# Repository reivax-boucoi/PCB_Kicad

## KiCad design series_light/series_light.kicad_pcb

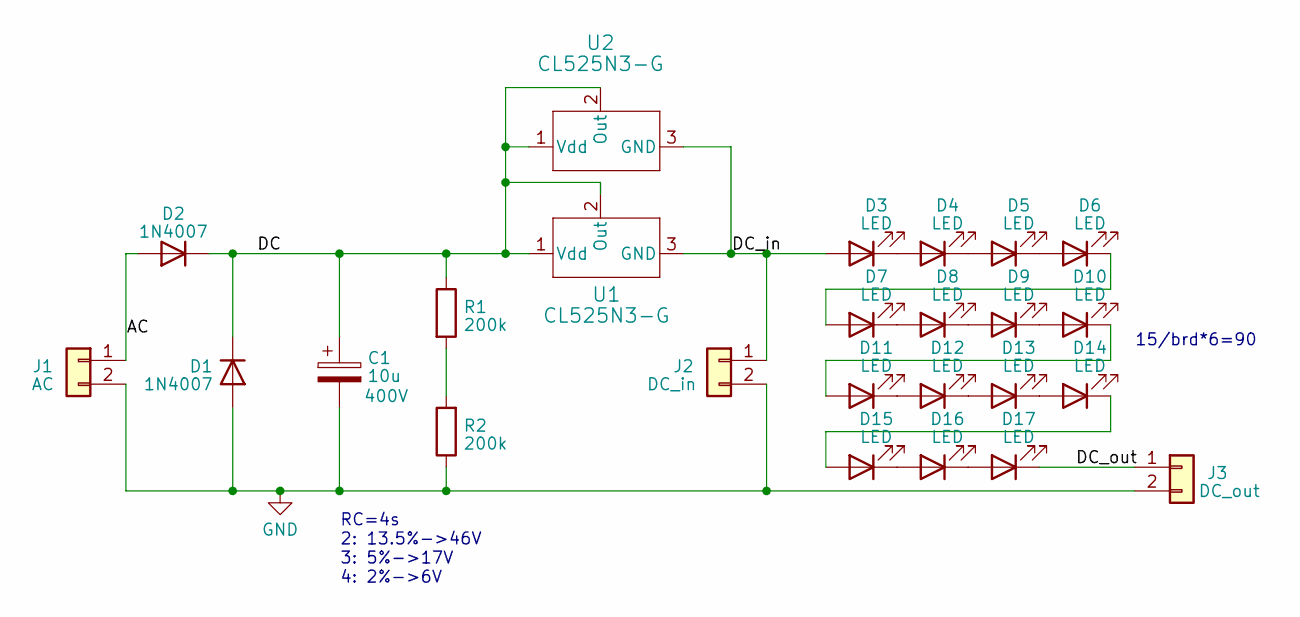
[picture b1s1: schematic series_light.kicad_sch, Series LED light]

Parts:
C1: 10u; Board_edge_cap_P5mm_D10mm; Voltage 400V
D1, D2: 1N4007; D_SMA
D3, D4, D5, D6, D7, D8, D9, D10, D11, D12, D13, D14, D15, D16, D17: LED; LED_PLCC_2835
J1: AC; TerminalBlock_bornier-2_P5.08mm
J2: DC_in; Board_chain_Conn
J3: DC_out; Board_chain_Conn
R1, R2: 200k; R_0805_2012Metric
U1, U2: CL525N3-G; TO-92

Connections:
/AC: D2.2 (A), J1.1
/DC: C1.1, D1.1 (K), D2.1 (K), R1.1, U1.1 (Vdd), U1.2 (Out), U2.1 (Vdd), U2.2 (Out)
/DC_in: D3.2 (A), J2.1, U1.3 (GND), U2.3 (GND)
/DC_out: D17.1 (K), J3.1
GND: C1.2, D1.2 (A), J1.2, J2.2, J3.2, R2.1
unnamed: D3.1 (K), D4.2 (A)
unnamed: D4.1 (K), D5.2 (A)
unnamed: D5.1 (K), D6.2 (A)
unnamed: D6.1 (K), D7.2 (A)
unnamed: D7.1 (K), D8.2 (A)
unnamed: D8.1 (K), D9.2 (A)
unnamed: D9.1 (K), D10.2 (A)
unnamed: D10.1 (K), D11.2 (A)
unnamed: D11.1 (K), D12.2 (A)
unnamed: D12.1 (K), D13.2 (A)
unnamed: D13.1 (K), D14.2 (A)
unnamed: D14.1 (K), D15.2 (A)
unnamed: D15.1 (K), D16.2 (A)
unnamed: D16.1 (K), D17.2 (A)
unnamed: R1.2, R2.2

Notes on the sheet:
RC=4s 2: 13.5%->46V 3: 5%->17V 4: 2%->6V
15/brd*6=90

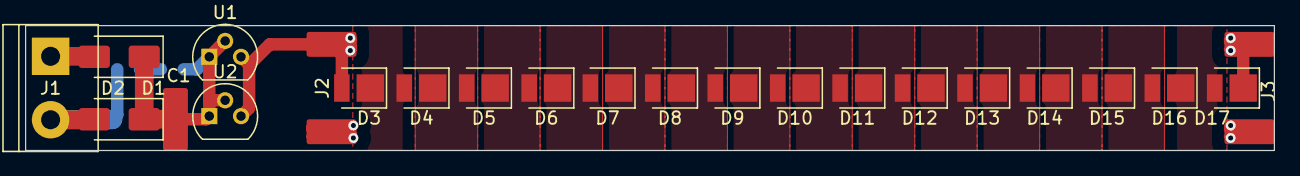
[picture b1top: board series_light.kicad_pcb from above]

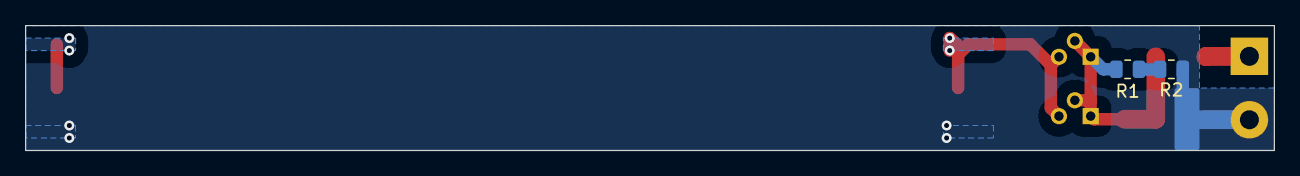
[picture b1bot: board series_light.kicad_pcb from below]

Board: 2 copper layers, 100.0 x 10.0 mm, 25 parts (2 on the bottom side), 20 nets.

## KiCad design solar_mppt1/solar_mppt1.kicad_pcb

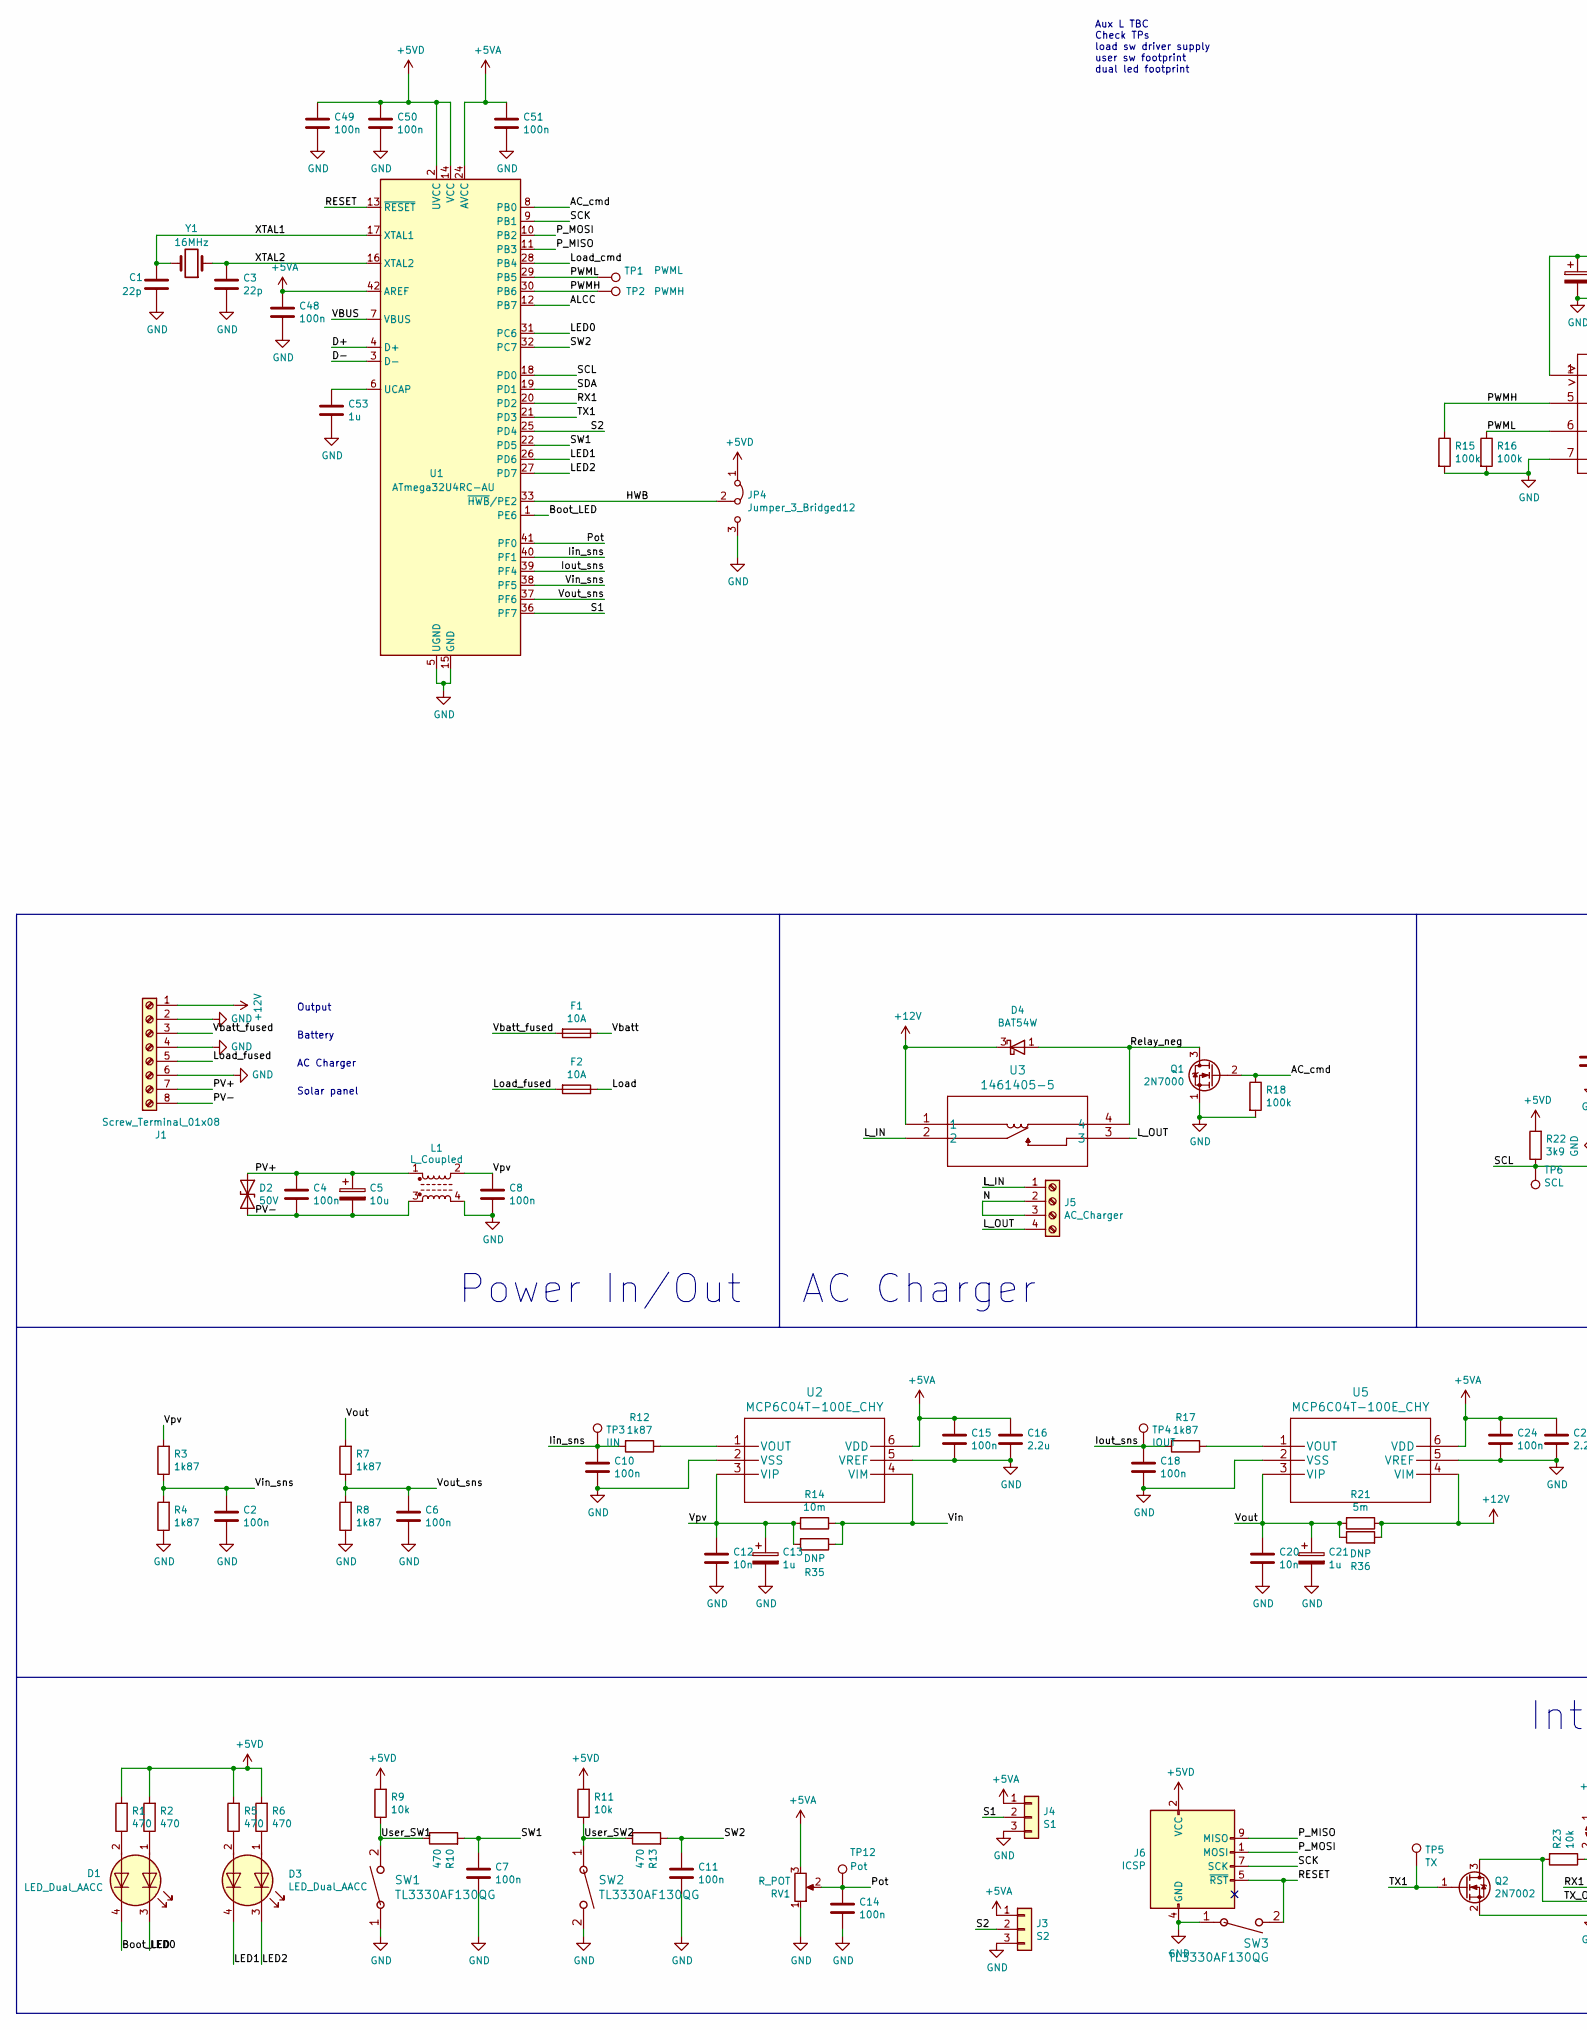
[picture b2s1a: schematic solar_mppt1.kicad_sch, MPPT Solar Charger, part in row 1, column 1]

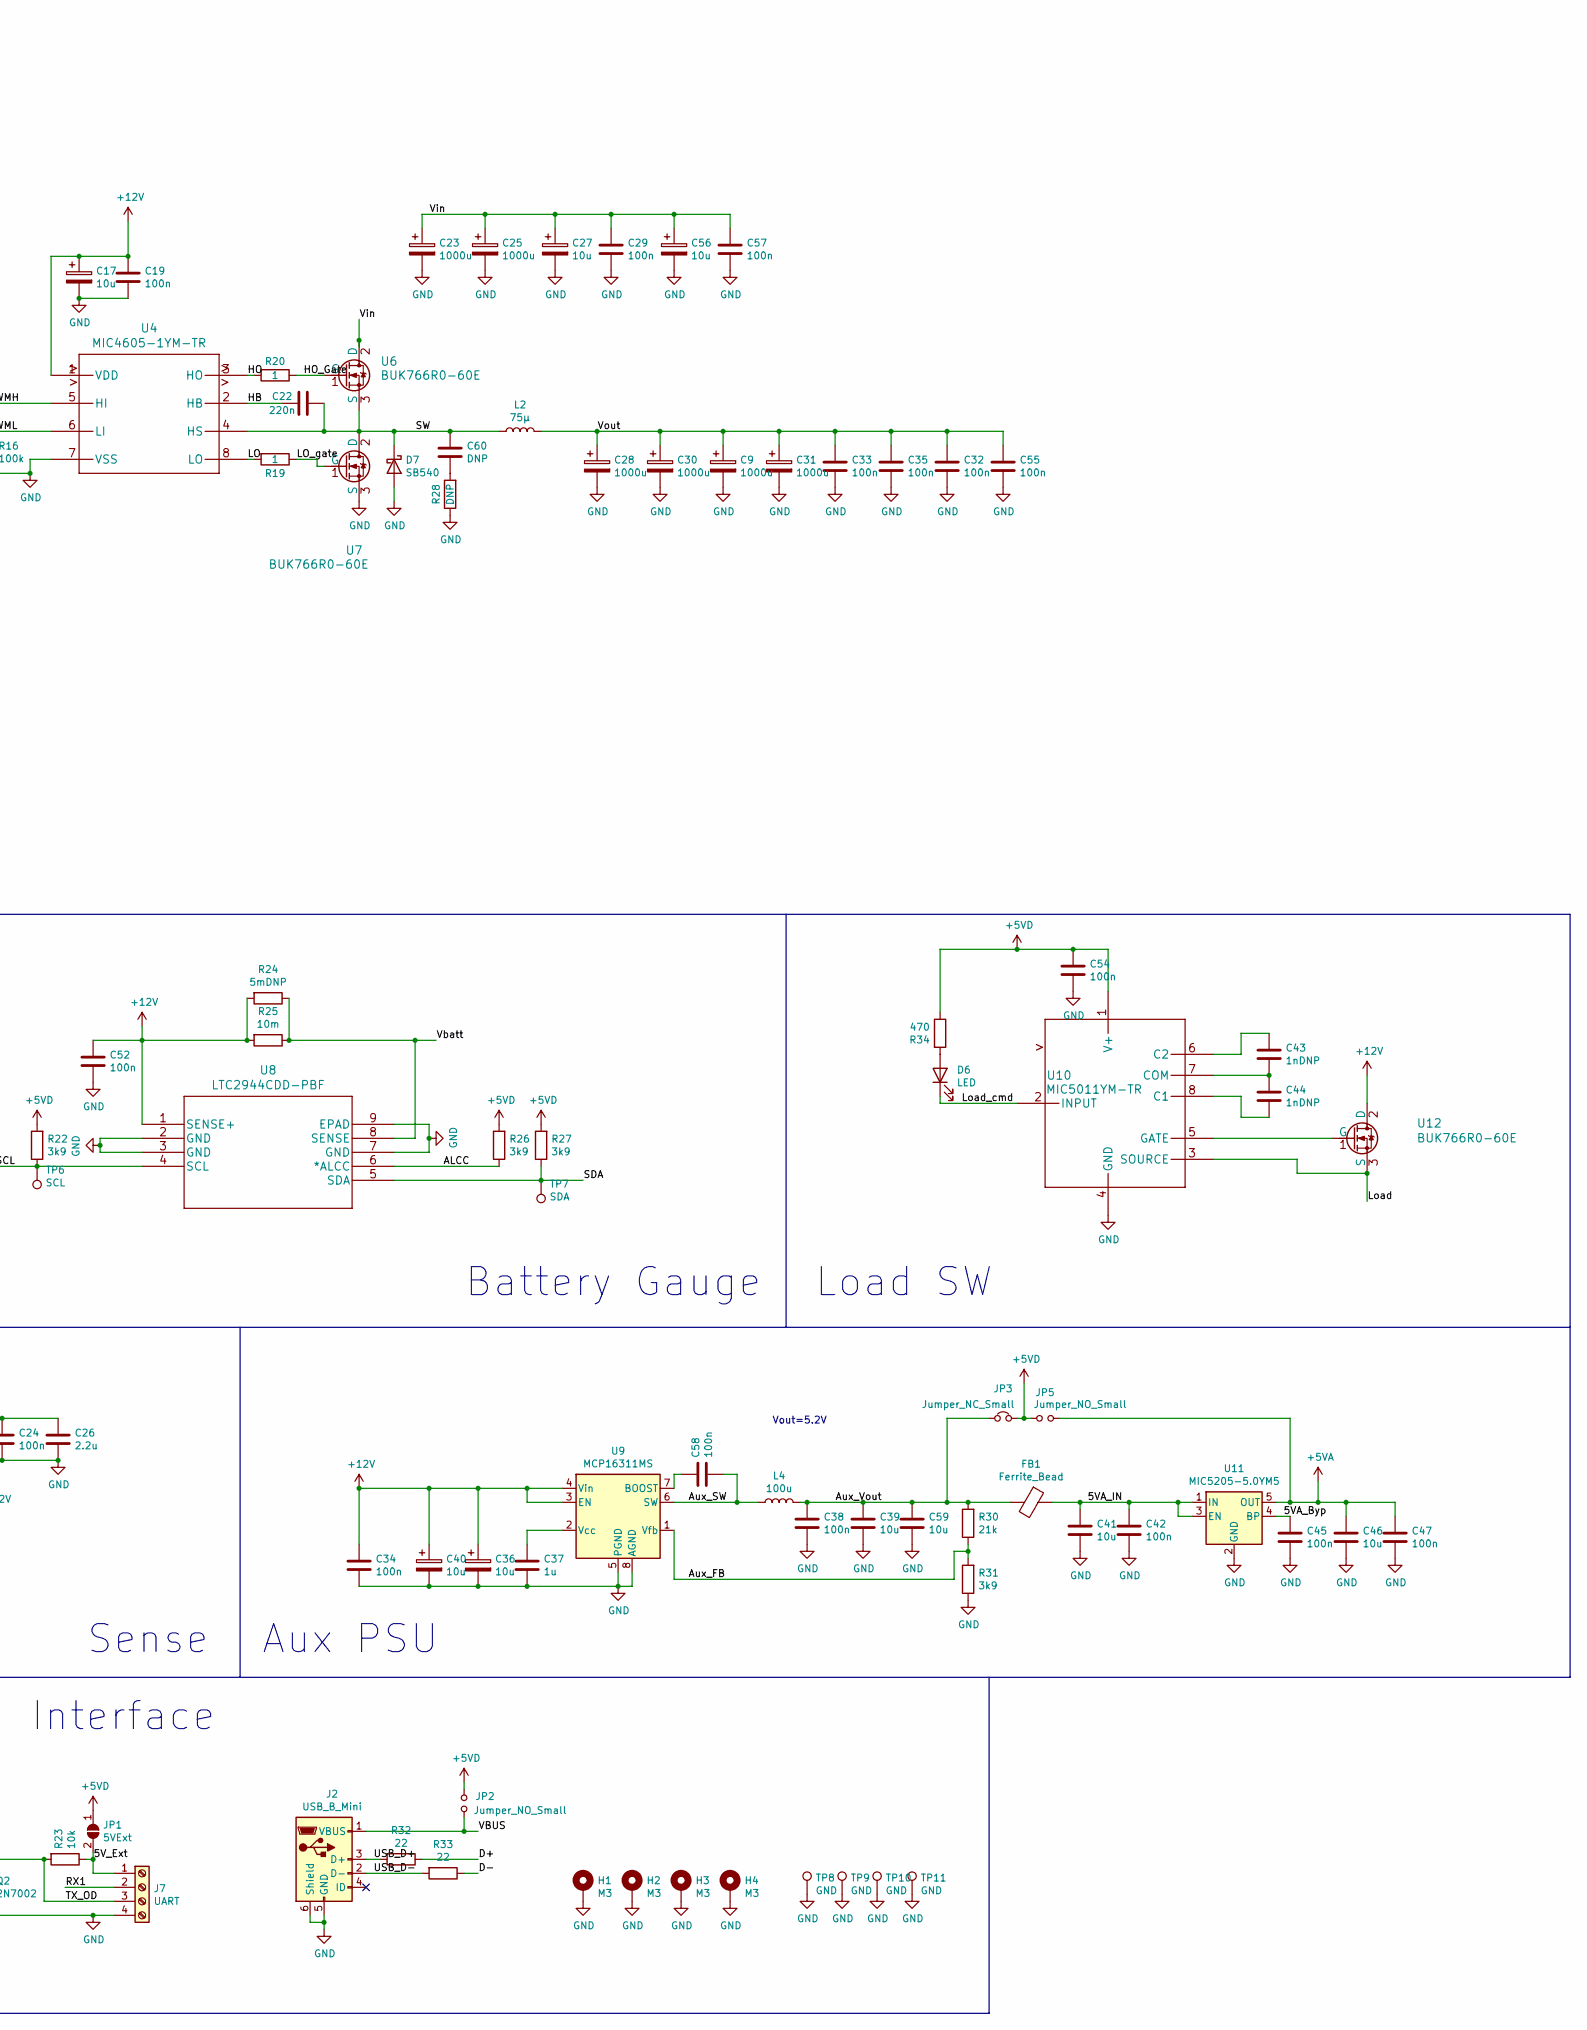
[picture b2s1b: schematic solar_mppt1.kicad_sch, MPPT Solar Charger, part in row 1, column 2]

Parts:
C1, C3: 22p; C_0603_1608Metric_Pad1.05x0.95mm_HandSolder
C2, C4, C6, C7, C8, C10, C11, C14, C15, C18, C19, C24, C29, C32, C33, C34, C35, C38, C42, C45, C47, C48, C49, C50, C51, C52, C54, C55, C57, C58: 100n; C_0603_1608Metric_Pad1.05x0.95mm_HandSolder
C5, C17, C27, C36, C40, C56: 10u; CP_Radial_D5.0mm_P2.00mm
C9, C28, C30, C31: 1000u; CP_Radial_D10.0mm_P5.00mm
C12, C20: 10n; C_0805_2012Metric_Pad1.15x1.40mm_HandSolder
C13, C21: 1u; CP_Radial_D5.0mm_P2.00mm
C16, C26: 2.2u; C_0805_2012Metric_Pad1.15x1.40mm_HandSolder
C22: 220n; C_Rect_L7.0mm_W2.5mm_P5.00mm
C23, C25: 1000u; CP_Radial_D16.0mm_P7.50mm
C37: 1u; C_0603_1608Metric_Pad1.05x0.95mm_HandSolder
C39, C41, C46, C59: 10u; C_0805_2012Metric_Pad1.15x1.40mm_HandSolder
C43, C44: 1nDNP; C_0603_1608Metric_Pad1.05x0.95mm_HandSolder
C53: 1u; C_0805_2012Metric_Pad1.15x1.40mm_HandSolder
C60: DNP; C_0603_1608Metric_Pad1.05x0.95mm_HandSolder
D1, D3: LED_Dual_AACC; LED_Cree-PLCC4_3.2x2.8mm_CCW
D2: 50V; D_5KPW_P7.62mm_Vertical_AnodeUp
D4: BAT54W; SOT-323_SC-70
D6: LED; LED_0603_1608Metric_Pad1.05x0.95mm_HandSolder
D7: SB540; D_DO-201AD_P5.08mm_Vertical_AnodeUp
F1, F2: 10A; Fuseholder_Cylinder-5x20mm_Stelvio-Kontek_PTF78_Horizontal_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
FB1: Ferrite_Bead; FerriteBead
H1, H2, H3, H4: M3; MountingHole_3.2mm_M3_Pad_Via
J1: Screw_Terminal_01x08; TerminalBlock_Phoenix_MKDS-1,5-8-5.08_1x08_P5.08mm_Horizont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
J2: USB_B_Mini; USB_Mini-B_Lumberg_2486_01_Horizontal
J3: S2; PinHeader_1x03_P2.54mm_Vertical
J4: S1; PinHeader_1x03_P2.54mm_Vertical
J5: AC_Charger; TerminalBlock_bornier-4_P5.08mm
J6: ICSP; IDC-Header_2x05_P2.54mm_Vertical
J7: UART; TerminalBlock_TE_282834-4_1x04_P2.54mm_Horizontal
JP1: 5VExt; SolderJumper-2_P1.3mm_Open_RoundedPad1.0x1.5mm
JP2, JP5: Jumper_NO_Small; SolderJumper-2_P1.3mm_Open_RoundedPad1.0x1.5mm
JP3: Jumper_NC_Small; SolderJumper-2_P1.3mm_Bridged_RoundedPad1.0x1.5mm
JP4: Jumper_3_Bridged12; SolderJumper-3_P1.3mm_Bridged12_RoundedPad1.0x1.5mm
L1: L_Coupled; Choke_toroidal
L2: 75µ; L_Toroid_Vertical_L26.7mm_W14.0mm_P10.16mm_Pulse_D
L4: 100u; LPC4545
Q1: 2N7000; TO-92_Inline
Q2: 2N7002; SOT-23
R1, R2, R5, R6, R10, R13, R34: 470; R_0603_1608Metric_Pad1.05x0.95mm_HandSolder
R3, R4, R7, R8, R12, R17: 1k87; R_0603_1608Metric_Pad1.05x0.95mm_HandSolder
R9, R11, R23: 10k; R_0805_2012Metric_Pad1.15x1.40mm_HandSolder
R14, R25: 10m; R_2512_6332Metric_Pad1.52x3.35mm_HandSolder
R15, R16, R18: 100k; R_0805_2012Metric_Pad1.15x1.40mm_HandSolder
R19, R20: 1; R_0805_2012Metric_Pad1.15x1.40mm_HandSolder
R21: 5m; R_Bare_Metal_Element_L12.4mm_W4.8mm_P11.40mm
R22, R26, R27, R31: 3k9; R_0805_2012Metric_Pad1.15x1.40mm_HandSolder
R24: 5mDNP; R_Bare_Metal_Element_L12.4mm_W4.8mm_P11.40mm
R28: DNP; R_0805_2012Metric_Pad1.15x1.40mm_HandSolder
R30: 21k; R_0805_2012Metric_Pad1.15x1.40mm_HandSolder
R32, R33: 22; R_0805_2012Metric_Pad1.15x1.40mm_HandSolder
R35: DNP; R_Bare_Metal_Element_L12.4mm_W4.8mm_P11.40mm
R36: DNP; R_2512_6332Metric_Pad1.52x3.35mm_HandSolder
RV1: R_POT; Potentiometer_Bourns_3299W_Vertical
SW1, SW2, SW3: TL3330AF130QG; TL3330
TP1: PWML; TestPoint_THTPad_2.0x2.0mm_Drill1.0mm
TP2: PWMH; TestPoint_THTPad_2.0x2.0mm_Drill1.0mm
TP3: IIN; TestPoint_THTPad_2.0x2.0mm_Drill1.0mm
TP4: IOUT; TestPoint_THTPad_2.0x2.0mm_Drill1.0mm
TP5: TX; TestPoint_THTPad_2.0x2.0mm_Drill1.0mm
TP6: SCL; TestPoint_THTPad_2.0x2.0mm_Drill1.0mm
TP7: SDA; TestPoint_THTPad_2.0x2.0mm_Drill1.0mm
TP8, TP9, TP10, TP11: GND; TestPoint_THTPad_2.0x2.0mm_Drill1.0mm
TP12: Pot; TestPoint_THTPad_2.0x2.0mm_Drill1.0mm
U1: ATmega32U4RC-AU; TQFP-44_10x10mm_P0.8mm
U2, U5: MCP6C04T-100E_CHY; MCP6C04T-
U3: 1461405-5; OJ-SH-112LM_relay
U4: MIC4605-1YM-TR
U6, U7, U12: BUK766R0-60E
U8: LTC2944CDD-PBF
U9: MCP16311MS; MSOP-8_3x3mm_P0.65mm
U10: MIC5011YM-TR
U11: MIC5205-5.0YM5; SOT-23-5
Y1: 16MHz; Crystal_HC49-U_Vertical

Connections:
+5VA: C15.1, C16.1, C24.1, C26.1, C46.1, C47.1, C48.1, C51.1, J3.1, J4.1, JP5.2, RV1.3, U1.24 (AVCC), U1.42 (AREF), U1.44 (AVCC), U2.6 (VDD), U5.6 (VDD), U11.5 (OUT)
+5VD: C49.1, C50.1, C54.1, J6.2 (VCC), JP1.1 (A), JP2.2, JP3.2, JP4.1 (A), JP5.1, R1.2, R2.2, R5.2, R6.2, R9.2, R11.2, R22.2, R26.2, R27.2, R34.1, U1.2 (UVCC), U1.14 (VCC), U1.34 (VCC), U10.1 (V+)
+12V: C17.1, C19.1, C34.1, C36.1, C40.1, C52.1, D4.3 (K), J1.1, R21.1, R24.2, R25.2, R36.2, U3.1, U4.1 (VDD), U5.4 (VIM), U8.1 (SENSE+), U9.3 (EN), U9.4 (Vin), U12.2 (D)
/5VA_Byp: C45.1, U11.4 (BP)
/5VA_IN: C41.1, C42.1, FB1.1, U11.1 (IN), U11.3 (EN)
/5V_Ext: J7.1, JP1.2 (B), R23.1
/AC_cmd: Q1.2 (G), R18.1, U1.8 (PB0)
/ALCC: R26.1, U1.12 (PB7), U8.6 (*ALCC)
/Aux_FB: R30.1, R31.2, U9.1 (Vfb)
/Aux_SW: C58.2, L4.1, U9.6 (SW)
/Aux_Vout: C38.1, C39.1, C59.1, FB1.2, JP3.1, L4.2, R30.2
/Boot_LED: D1.4 (K2), U1.1 (PE6)
/D+: R32.1, U1.4 (D+)
/D-: R33.1, U1.3 (D-)
/HB: C22.2, U4.2 (HB)
/HO: R20.2, U4.3 (HO)
/HO_Gate: R20.1, U6.1 (G)
/HWB: JP4.2 (C), U1.33 (~HWB/PE2)
/Iin_sns: C10.1, R12.2, TP3.1, U1.40 (PF1)
/Iout_sns: C18.1, R17.2, TP4.1, U1.39 (PF4)
/L: J5.1, U3.2
/LED0: D1.3 (K1), U1.31 (PC6)
/LED1: D3.4 (K2), U1.26 (PD6)
/LED2: D3.3 (K1), U1.27 (PD7)
/LO: R19.2, U4.8 (LO)
/LO_gate: R19.1, U7.1 (G)
/L_OUT: J5.4, U3.3
/Load: F2.1, U10.3 (SOURCE), U12.3 (S)
/Load_cmd: D6.1 (K), U1.28 (PB4), U10.2 (INPUT)
/Load_fused: F2.2, J1.5
/N: J5.2, J5.3
/PV+: C4.1, C5.1, D2.1 (A1), J1.7, L1.1
/PV-: C4.2, C5.2, D2.2 (A2), J1.8, L1.3
/PWMH: R15.1, TP2.1, U1.30 (PB6), U4.5 (HI)
/PWML: R16.1, TP1.1, U1.29 (PB5), U4.6 (LI)
/P_MISO: J6.9 (MISO), U1.11 (PB3)
/P_MOSI: J6.1 (MOSI), U1.10 (PB2)
/Pot: C14.1, RV1.2, TP12.1, U1.41 (PF0)
/RESET: J6.5 (~RST), SW3.2, U1.13 (~RESET)
/RX1: J7.2, U1.20 (PD2)
/Relay_neg: D4.1 (A), Q1.3 (D), U3.4
/S1: J4.2, U1.36 (PF7)
/S2: J3.2, U1.25 (PD4)
/SCK: J6.7 (SCK), U1.9 (PB1)
/SCL: R22.1, TP6.1, U1.18 (PD0), U8.4 (SCL)
/SDA: R27.1, TP7.1, U1.19 (PD1), U8.5 (SDA)
/SW: C22.1, C60.1, D7.1 (K), L2.1, U4.4 (HS), U6.3 (S), U7.2 (D)
/SW1: C7.1, R10.2, U1.22 (PD5)
/SW2: C11.1, R13.2, U1.32 (PC7)
/TX1: Q2.1 (G), TP5.1, U1.21 (PD3)
/TX_OD: J7.3, Q2.3 (D), R23.2
/USB_D+: J2.3 (D+), R32.2
/USB_D-: J2.2 (D-), R33.2
/User_SW1: R9.1, R10.1, SW1.2
/User_SW2: R11.1, R13.1, SW2.1
/VBUS: J2.1 (VBUS), JP2.1, U1.7 (VBUS)
/Vbatt: F1.1, R24.1, R25.1, U8.8 (SENSE)
/Vbatt_fused: F1.2, J1.3
/Vin: C23.1, C25.1, C27.1, C29.1, C56.1, C57.1, R14.1, R35.1, U2.4 (VIM), U6.2 (D)
/Vin_sns: C2.1, R3.1, R4.2, U1.38 (PF5)
/Vout: C9.1, C20.1, C21.1, C28.1, C30.1, C31.1, C32.1, C33.1, C35.1, C55.1, L2.2, R7.2, R21.2, R36.1, U5.3 (VIP)
/Vout_sns: C6.1, R7.1, R8.2, U1.37 (PF6)
/Vpv: C8.1, C12.1, C13.1, L1.2, R3.2, R14.2, R35.2, U2.3 (VIP)
/XTAL1: C1.1, U1.17 (XTAL1), Y1.2
/XTAL2: C3.1, U1.16 (XTAL2), Y1.1
GND: C1.2, C2.2, C3.2, C6.2, C7.2, C8.2, C9.2, C10.2, C11.2, C12.2, C13.2, C14.2, C15.2, C16.2, C17.2, C18.2, C19.2, C20.2, C21.2, C23.2, C24.2, C25.2, C26.2, C27.2, C28.2, C29.2, C30.2, C31.2, C32.2, C33.2, C34.2, C35.2, C36.2, C37.2, C38.2, C39.2, C40.2, C41.2, C42.2, C45.2, C46.2, C47.2, C48.2, C49.2, C50.2, C51.2, C52.2, C53.2, C54.2, C55.2, C56.2, C57.2, C59.2, D7.2 (A), H1.1, H2.1, H3.1, H4.1, J1.2, J1.4, J1.6, J2.5 (GND), J2.6 (Shield), J3.3, J4.3, J6.4 (GND), J6.6 (GND), J6.8 (GND), J6.10 (GND), J7.4, JP4.3 (B), L1.4, Q1.1 (S), Q2.2 (S), R4.1, R8.1, R15.2, R16.2, R18.2, R28.1, R31.1, RV1.1, SW1.1, SW2.2, SW3.1, TP8.1, TP9.1, TP10.1, TP11.1, U1.5 (UGND), U1.15 (GND), U1.23 (GND), U1.35 (GND), U1.43 (GND), U2.2 (VSS), U2.5 (VREF), U4.7 (VSS), U5.2 (VSS), U5.5 (VREF), U7.3 (S), U8.2 (GND), U8.3 (GND), U8.7 (GND), U8.9 (EPAD), U9.5 (PGND), U9.8 (AGND), U10.4 (GND), U11.2 (GND)
unnamed: C37.1, U9.2 (Vcc)
unnamed: C43.1, U10.6 (C2)
unnamed: C43.2, C44.1, U10.7 (COM)
unnamed: C44.2, U10.8 (C1)
unnamed: C53.1, U1.6 (UCAP)
unnamed: C58.1, U9.7 (BOOST)
unnamed: C60.2, R28.2
unnamed: D1.1 (A1), R2.1
unnamed: D1.2 (A2), R1.1
unnamed: D3.1 (A1), R6.1
unnamed: D3.2 (A2), R5.1
unnamed: D6.2 (A), R34.2
unnamed: R12.1, U2.1 (VOUT)
unnamed: R17.1, U5.1 (VOUT)
unnamed: U10.5 (GATE), U12.1 (G)

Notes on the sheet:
Battery Gauge
Sense
AC Charger
Interface
Vout=5.2V
Aux PSU
Solar panel
Output
Power In/Out
Battery
Load SW
Aux L TBC Check TPs load sw driver supply user sw footprint dual led footprint

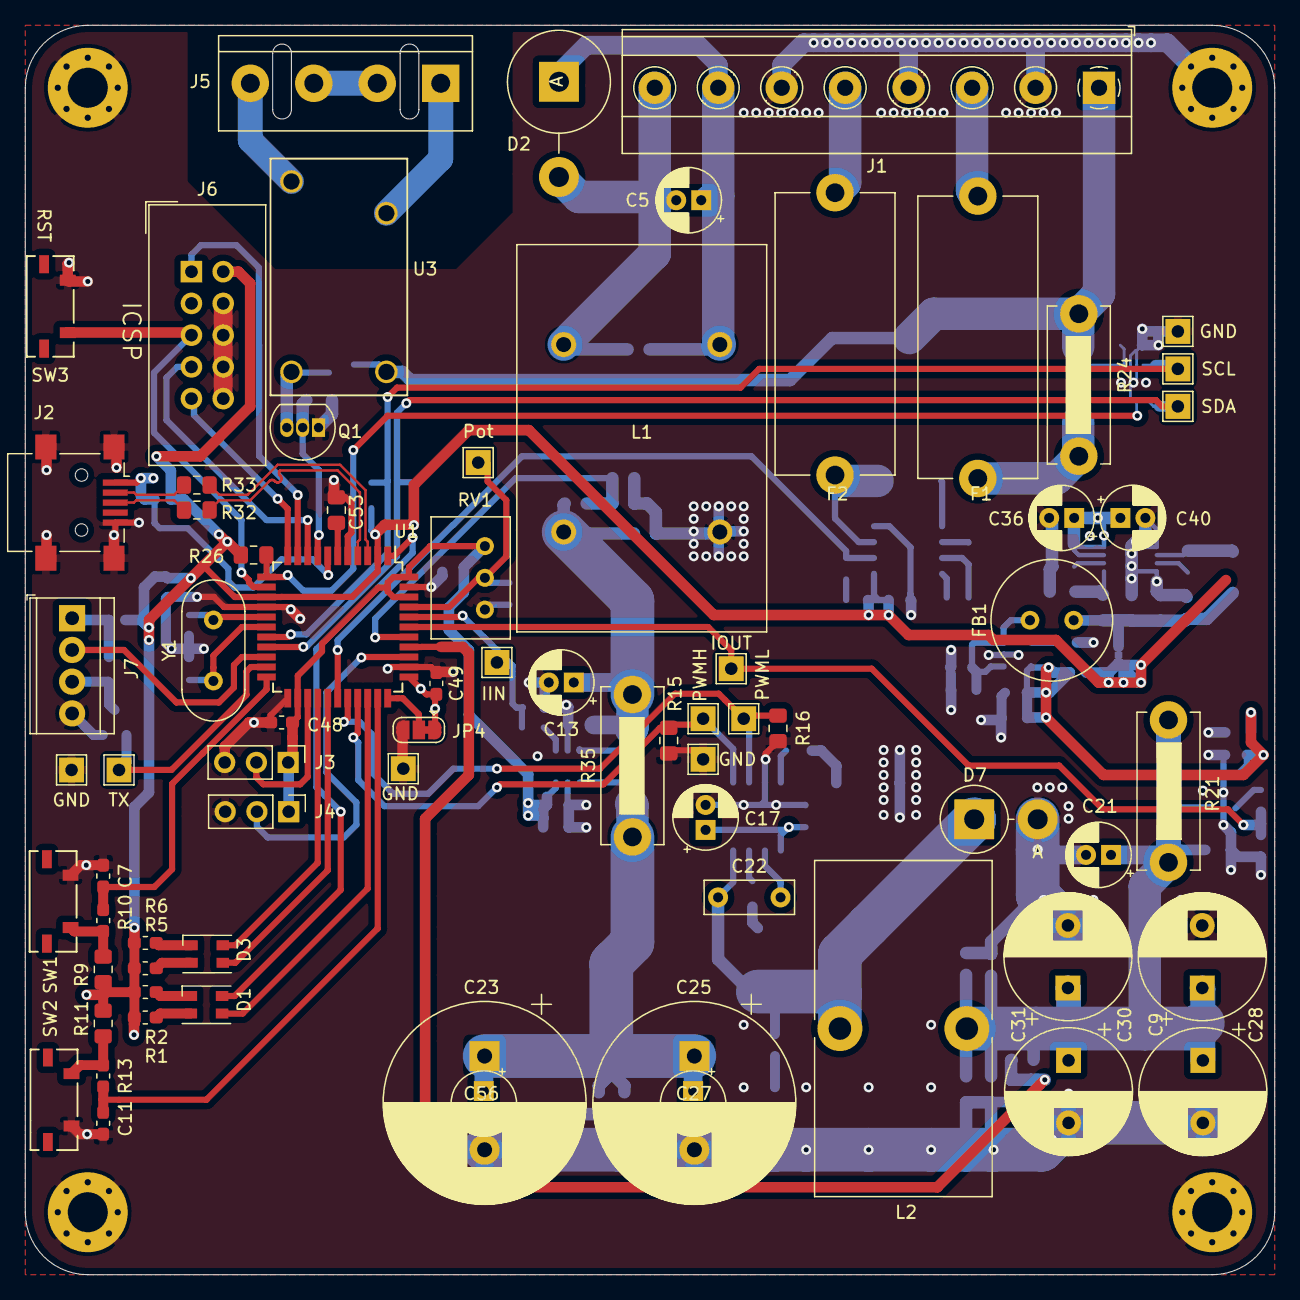
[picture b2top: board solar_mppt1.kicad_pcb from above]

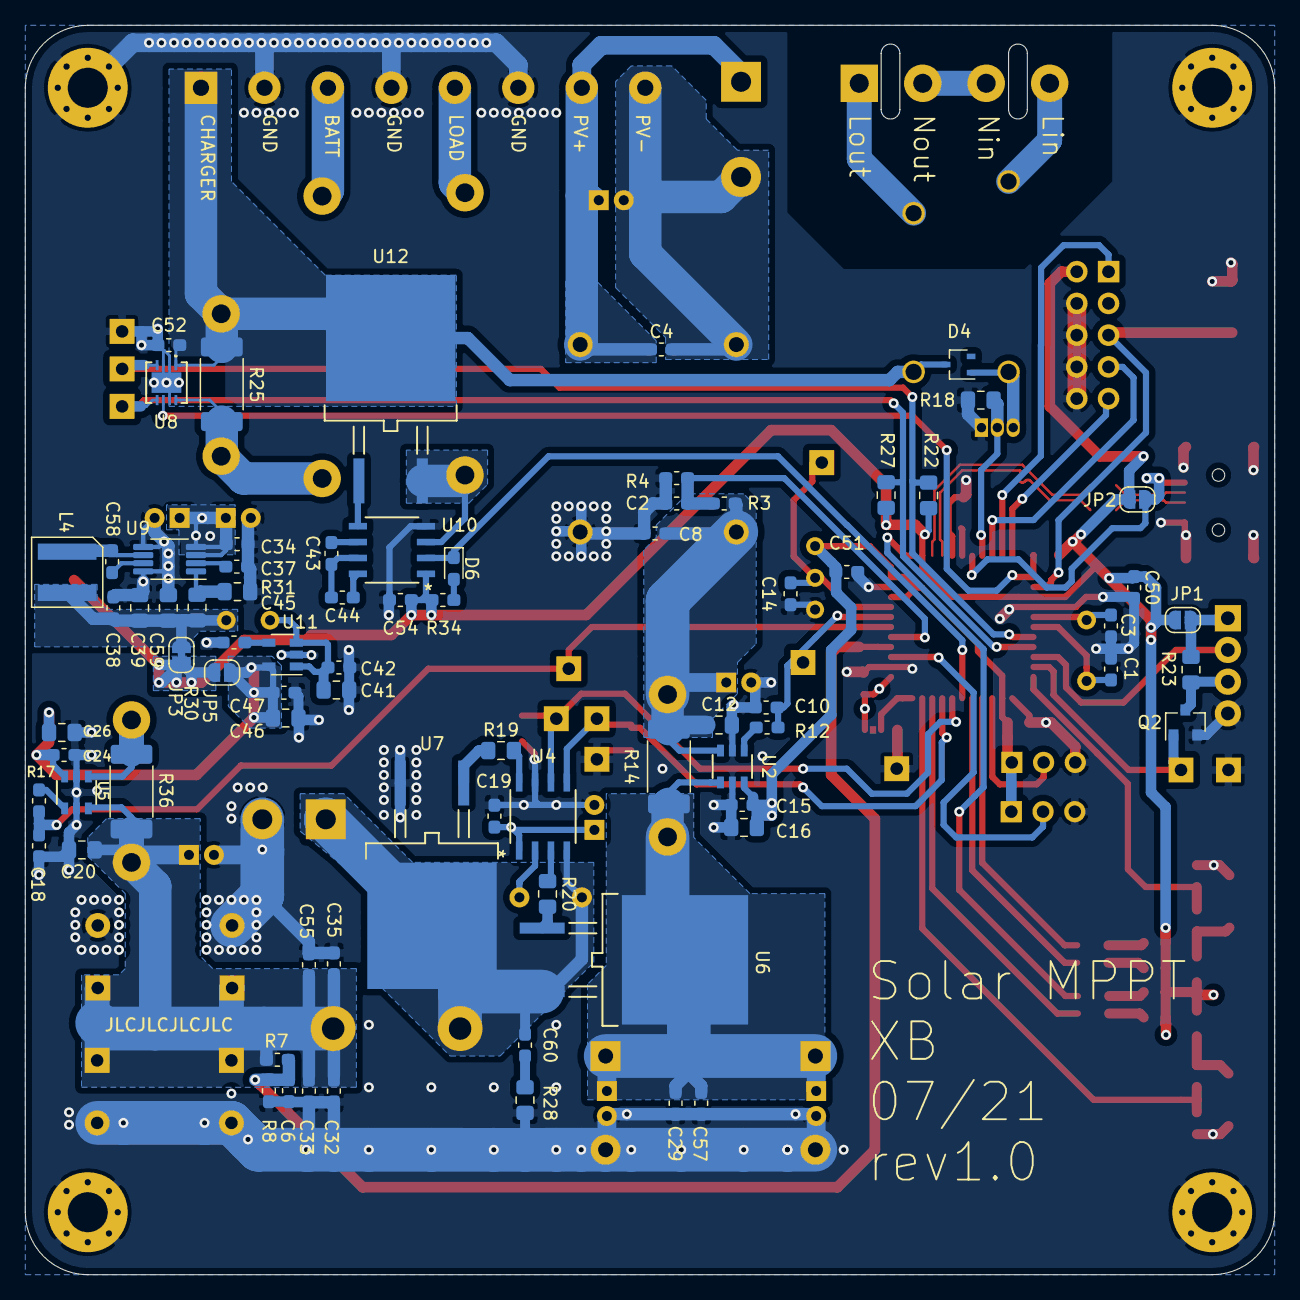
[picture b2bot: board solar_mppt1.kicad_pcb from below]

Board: 4 copper layers, 100.0 x 100.0 mm, 154 parts (77 on the bottom side), 81 nets.

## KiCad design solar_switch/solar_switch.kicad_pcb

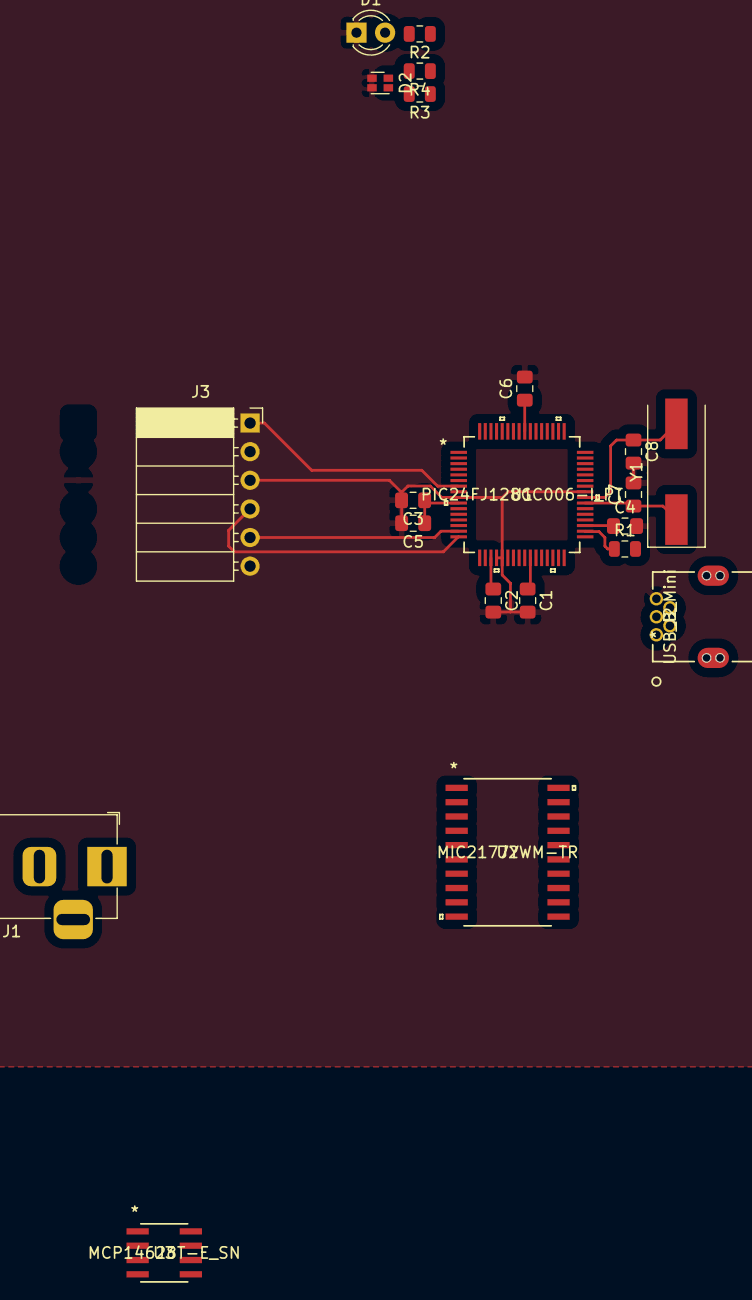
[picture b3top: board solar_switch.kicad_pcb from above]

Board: 2 copper layers, 21 parts (0 on the bottom side), 21 nets.

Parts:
C1, C2, C3, C4: 100n; C_0805_2012Metric_Pad1.15x1.40mm_HandSolder
C5, C6: 10u; C_0805_2012Metric_Pad1.15x1.40mm_HandSolder
C7, C8: 15p; C_0805_2012Metric_Pad1.15x1.40mm_HandSolder
D1: LED; LED_D3.0mm
D2: LED_Dual_AACC; LED_LiteOn_LTST-C19HE1WT
J1: Jack-DC; BarrelJack_Horizontal
J2: USB_B_Mini; 54819-0519
J3: Conn_PIC_ICSP_ICD; PinSocket_1x06_P2.54mm_Horizontal
R1: 100; R_0805_2012Metric
R2, R3, R4: 470; R_0805_2012Metric
U1: PIC24FJ128GC006-I_PT; PIC24FJ128GC006-I&slash_PT
U2: MIC2177YWM-TR
U3: MCP14628T-E_SN; MCP14628T-E&slash_SN
Y1: Crystal; Crystal_SMD_HC49-SD

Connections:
+3V3: C3.1, C4.1, C5.1, J3.2, U1.10, U1.35, U1.38, U1.57
/AVDD: C2.1, U1.19
/D+: J2.3, U1.37
/D-: J2.2, U1.36
/MCLR: J3.1, U1.7
/PGEC1: J3.5, U1.15
/PGED1: J3.4, U1.16
/SVDD: C1.1, U1.26
/Vcap: C6.1, U1.56
GND: C1.2, C2.2, C3.2, C4.2, C5.2, C6.2, C7.2, C8.2, D1.1, D2.3, D2.4, J2.5, J3.3, U1.9, U1.20, U1.21, U1.41
unnamed: C7.1, U1.39, Y1.1
unnamed: C8.1, U1.40, Y1.2
unnamed: D1.2, R2.2
unnamed: D2.1, R4.2
unnamed: D2.2, R3.2
unnamed: J2.1, R1.2
unnamed: U2.1, U2.2, U2.9
unnamed: U2.3, U2.8
unnamed: U2.4, U2.5, U2.6, U2.7
unnamed: U2.14, U2.15, U2.16, U2.17
VBUS: R1.1, U1.34

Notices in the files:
parts and their libraries:
Copyright 2016 Accelerated Designs. All rights reserved.
